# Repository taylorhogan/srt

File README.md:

# Iris — a robotic telescope you talk to

*IC 1396A, the Elephant's Trunk — 12.1 hours across four nights: 145
five-minute exposures through three narrowband filters. Nobody was in the
observatory for any of them.*

Text Iris the name of a nebula from your phone. Some clear night — maybe tonight,
maybe next week when the geometry is right — a roof in a backyard opens on its
own, a half-ton telescope wakes up, finds the target, and spends the dark hours
collecting photons that left their source before the pyramids were built. By
breakfast there is a finished picture on your phone, captioned with how many
frames survived the night's quality gate. Nobody was in the observatory. Nobody
was awake.

That is the whole idea: **a fully autonomous deep-sky observatory run by
conversation**, built on one stubborn principle — *measure it, or it isn't
true*. Every subsystem below exists because a measurement demanded it, and most
of them have caught at least one thing that "looked fine."

The pictures and the write-ups live at **[irisscience.org](https://irisscience.org)**:
a gallery, a lab notebook of about thirty science notes (linked throughout this
page), and a live tab showing what the observatory is doing *right now*, down to
which state of its night state machine it is standing in.

---

## Hubble's experiment, a century later

In October 1923 Edwin Hubble found a Cepheid variable on a plate of the
Andromeda nebula, timed its 31.4-day pulse, and from Henrietta Leavitt's
period–luminosity law measured the distance to another galaxy for the first
time. In the autumn of 2026 Iris ran the same measurement on the same star.

- The star went into the queue on October 8 as a one-hour *monitor* target with
  its period attached. From then on the planner gave it an hour near the zenith
  on every clear night, the frames were calibrated and measured against Gaia
  comparison stars each morning, and the pipeline's own coverage rule decided
  when the curve was complete.
- Twenty-two nights caught the whole cycle: a 1.1-magnitude swing, the first
  maximum, the long decline, and a second climb of a full magnitude in two
  nights. The fitted curve's predictions for coming nights were kept and tested;
  three of four landed within a few hundredths, and the one miss is the most
  instructive line in the note.
- Leavitt's law, as calibrated by Hubble Space Telescope parallaxes, turns the
  period and the mean brightness into **669 kpc, 2.18 million light years**,
  against 2.54 accepted — within a fifth with one star, one filter and a
  17-inch telescope. Hubble, with the 100-inch, got a factor of three too close;
  the difference is a century of calibration, not the glass.
- The nightly measurements are AAVSO-grade (calibrated, saturation-guarded,
  airmass on every record, obstructed frames dropped) and written in the
  association's format for upload.

→ [Hubble's Star, a Century Later](https://irisscience.org/#hubble-v1-distance)
· [First light curves: Hubble's star and three Cepheids in Cassiopeia](https://irisscience.org/#cepheids-first-curves)
· [Three targets a night](https://irisscience.org/#three-slots) (how the hour was found)

---

## Neural networks trained on this sky

There is no clean reference image of the sky, so every network below
manufactures its own training signal from this telescope's own stacks, runs on
the observatory's GPU box, and is held to the same rule as everything else:
**nothing is ever measured from a network's output.** Every number quoted
anywhere comes from the calibrated linear stacks.

| Network | What it learns | Note |
|---|---|---|
| **Noise2Noise denoiser** | A U-Net trained on pairs of noisy stacks of the same field, no clean target ever seen. Runs every morning on the night's stacks; display only. | [Learning to denoise without ever seeing a clean image](https://irisscience.org/#noise2noise) · [The first denoise worth showing](https://irisscience.org/#n2n-first-result) |
| **Learned deconvolution** | Each stack is blurred a second time with its own measured kernel and the network learns to take that blur back off. It does not paint pixels: for every pixel it decides where the light came from and sends it back, so light is moved, never made, and stars go from 7.5 to about 4 px with no rings. Now the default sharpening on every morning render. | [Learning to undo the blur: a network that moves light](https://irisscience.org/#learned-deblur) · [Deconvolving Stephan's Quintet](https://irisscience.org/#quintet-deblur) (the hand-rule version it replaced) |
| **Star / nebula split** | A U-Net that takes a narrowband plane and returns it without its stars; the stars are the difference. Trained on real backgrounds with known stars injected from the field's own star profile. On a field it had never seen it lifted 338 of 358 stars cleanly. | [IC 410 without its stars](https://irisscience.org/#starless-ic410) |
| **Two language models** | An open-weight vision-language model on the observatory's own computer reads the picture and the measured record and drafts the gallery entry in the house voice; a second model from a different lab checks it for errors. Nothing leaves the building. | [Who writes the caption](https://irisscience.org/#machine-caption) |

---

## Other things Iris has actually done

- **Measured a redshift with no spectrograph.** The four distant members of
  Stephan's Quintet recede fast enough that their hydrogen glow lands inside a
  3 nm filter built for sulfur; the foreground galaxy's does not. 56 times the
  noise in NGC 7319, nothing in NGC 7320.
  → [Five galaxies that only look like neighbors](https://irisscience.org/#quintet-redshift)
- **Identified an asteroid that wandered through a frame.** A rainbow of
  dashes under NGC 1055 tracked at 32.6 arcseconds an hour; solved against
  Gaia, it sat 1.3 arcseconds from where JPL put 464 Megaira.
  → [A visitor in the frame](https://irisscience.org/#asteroid-megaira)
- **Detected an exoplanet.** A 7-hour run on HAT-P-32 caught the transit of
  HAT-P-32b; the blind search ranked it first of 622 stars.
  → [Finding a planet by watching a star get 2% fainter](https://irisscience.org/#transit-search)
  · [A search that finds nothing looks exactly like a search that works](https://irisscience.org/#injection)
- **Decides for itself when a target is done and which filters to shoot.**
  A target is retired when its stack has stopped improving *and* every filter
  holds its minimum of good frames; each night's filter ratio goes to whatever
  the stack is shortest of, weighted by noise, seeing and moon. Live since
  November 2026; the first noon retired two targets.
  → [Two decisions the telescope now makes by itself](https://irisscience.org/#auto-stop-filters)
- **Fills the whole night.** Trees bound the sky at 60° west and 48° northeast;
  the planner fits three targets around them, and a light-curve target can ask
  for a single hour.
  → [Three targets a night](https://irisscience.org/#three-slots)
- **Knows where focus will be before it looks.** 580 autofocus runs showed every
  filter's focus follows temperature along a line, about 80 steps per degree;
  each filter block now starts at the model's prediction.
  → [Telling the telescope where focus will be](https://irisscience.org/#focus-seed)
- **Fixed its own color from the stars.** The camera records a fifth more green
  than red or blue for a white star; a few hundred field stars now set the
  white balance of every broadband render.
  → [Why the galaxy came out green, and how the stars fixed it](https://irisscience.org/#star-white-balance)
- **Caught a space station with a $25 camera.** The driveway camera knew the
  pass from that morning's orbital data, armed itself and recorded Tiangong
  through cloud on a night the roof never opened. The same camera is
  plate-solved to 1.5 px and called a real storm 25–40 minutes before the
  weather API.
  → [The $25 camera that caught a space station](https://irisscience.org/#satellite-tracker)
  · [A security camera as a scientific instrument](https://irisscience.org/#skycam)
- **Caught its own tooling lying.** The FITS headers showed the guider's dither
  silently dead in one axis for months; the mount was exonerated by direct
  measurement and the dither now runs through the mount's native API.
  → [Missing on purpose](https://irisscience.org/#dither)
- **Hears and watches its roof.** Every roof move is fingerprinted by sound and
  by a watt-by-watt power trace; a live stall watchdog cut motor power on a
  real gear-didn't-engage event.
  → [Teaching the observatory to hear its own roof failing](https://irisscience.org/#roof-sentry)
  · [The camera that has to be right about the roof](https://irisscience.org/#vision-safety)
- **Weighed a cluster's age, measured its own optics, and worked out what its
  seeing actually depends on** (850 hPa wind and humidity, not the jet stream).
  → [M13's color–magnitude diagram](https://irisscience.org/#hr-diagram)
  · [What shape is a star?](https://irisscience.org/#psf)
  · [Has anything changed, or was it just a bad night?](https://irisscience.org/#optics)
- **Put a status light on the nightstand** so the owner stops unlocking a phone
  at 2 a.m.: a five-centimeter screen that can do nothing but show the frame
  counts and the sky.
  → [A telescope status light for the nightstand](https://irisscience.org/#nightstand-display)

And one essay with no telescope time in it:
[What a year of a great telescope costs, and who pays it](https://irisscience.org/#telescope-cost).

---

## How a night works

1. **Noon** — the conductor's clock makes the decision: every queued target is
   scored by visibility above the measured tree line, air mass, priority and
   the moon, the night is cut into up to three slots, each slot's filter ratio
   is chosen from the frames already on disk and the seeing forecast, and the
   plan is journaled and posted. Disk space on either machine is a stopping item.
2. **Pre-sunset** — weather, safety flags and a fresh camera read are checked
   again; the N.I.N.A sequence is generated from the plan and compared, field
   by field, with what was announced. A mismatch refuses the file rather than
   the night.
3. **Roof open** — only after two cameras agree the scope is parked. The two
   hardware laws are absolute and enforced in code: *the roof never moves unless
   the scope is confirmed parked; the scope never moves unless the roof is
   confirmed open.* Since September 2026 the roof's position is read from an
   AprilTag on the moving truss by a second camera that needs no light, and
   the inside camera may only veto.
4. **The run** — cool, slew, plate-solve, seed the focus from the temperature
   model, autofocus, then light frames until astronomical dawn with a dither
   between subs. Every incoming frame is measured (FWHM, star count, sky) and
   streamed to the chat and the public live page.
5. **Dawn** — flats, park, roof close, dehumidifier on, summary posted. The
   GPU box pulls the night's frames, stacks, denoises, deconvolves, white
   balances and crops, and pushes the picture to a phone. A converged target
   gets a final render with its own quality check, a drafted caption, and a
   chat card that publishes to the gallery on the word `approve`.

The whole night is driven by a formally specified state machine — a data
table with every state × event pair tested, including a 1,944-case sweep that
proves the roof invariant over the entire sensor-evidence space. It shadowed
real nights read-only through the summer; since October 2026 it decides both
hardware invariants and plans the nights, and the legacy scheduler only carries
out what it says. A hold rings the phone until acknowledged, and a held
observatory reminds its owner once a day until released. Deploys are gated the
same way: the observatory pulls a `release` branch that only advances when CI
is green, so a broken push can never reach the roof controls.

---

## Talking to it

The chat runs on a self-hosted web server (excellent from a phone) with live
job cards, frame previews and cancellable long commands. A taste:

| Command | What happens |
|---|---|
| `image <dso>` | Queue a target; it is scheduled when its night comes, typed as galaxy or nebula on the way in |
| `tonight` | Tonight's plan: slots, hours, filters, weather, moon, visible ISS passes |
| `suggest` | Ranked showpieces worth adding, scored on the next 30 nights' visibility, field fit and moon; nothing is queued without an `image` |
| `stats` / `latest` | Per-frame quality plots; the most recent sub, annotated |
| `snr <dso>` | Stack-convergence curves per filter — is this target *done*? |
| `filters <dso> … for N` | An explicit filter plan that expires after N imaged nights |
| `reopen` / `hold` / `moon` / `maxhours` / `type` | The queue's fields as commands; no hand edits of the JSON |
| `process <dso> <recipe>` | Calibrated LRGB / HALRGB / HOO / SHO stack on demand, with palette gain and tone |
| `aavso <dso>` | The monitor's light curve in AAVSO Extended Format |
| `optics` | Per-star fits → FWHM heatmap, coma, tilt and collimation scores from one frame |
| `transit <star>` | Photometric time series and box-fit transit search |
| `overhead` | Aircraft over the roof right now, from the public ADS-B feed |
| `approve <dso>` / `reject <dso>` | The one word that publishes a drafted gallery entry |
| `safe!` / `stop!` / `resolve!` | The human veto, always |

---

## The parts

| Subsystem | What it does |
|---|---|
| `iris/conductor` | The machine-as-data state machine: journal, guards, the clock that plans the night, the bell that rings the phone |
| Scheduler | Carries out the conductor's plan: generation, verification, imaging, shutdown |
| Vision safety | AprilTags on the scope and the roof, read by two cameras; the north camera decides the roof, the inside camera may veto |
| Frame watcher | Live FWHM / star count / sky analysis of every sub as it lands |
| Sequence generator | Patches N.I.N.A templates with target, coordinates, per-filter gain, focus seed and the planned filter ratio, then verifies the file against the announcement |
| Stacker | Calibration matched to the lights' gain, quality gate, astroalign registration in a process pool, tiled sigma-clip that levels frames to a common sky (skipping that step measured **8× worse than the photon limit**) |
| Color pipeline | Shared reference and shared stretch across filters, Hα excess into LRGB, palette gain, star-neutral palettes, star white balance, color planes matched to one star width, four-stage background removal |
| Photometry | Nightly light curves against Gaia comparison stars, phase coverage, Leavitt-law distance, AAVSO export |
| Auto-stop, filter advisor, suggestions | The three decisions that used to need a person every few days |
| Audio + current sentry | Spectrogram matching and power-signature analysis of every roof move, plus the live stall watchdog |
| Sky cameras | An all-sky fisheye and a plate-solved consumer cam: cloud cover, rain detection, satellite passes, limiting magnitude |
| Publisher | The live page, the target board, final renders with QC, drafted captions, the approve gate, the gallery |
| `nn/` | Noise2Noise, learned deconvolution and the star split: training and nightly inference on a DGX Spark |

Hardware: PlaneWave CDK17 on an L-500 direct-drive mount, a 61 MP full-frame
mono camera with a 7-filter wheel, a sliding roof driven by a gate-opener motor,
TP-Link/Shelly switched power, cameras and a microphone as senses, an NVIDIA
DGX Spark for the networks — all behind Tailscale, with the public face served
through a Cloudflare tunnel.

---

## A word of honesty before you clone

This is open source, but it is not (yet) a product. Iris is one specific
observatory — one roof, one mount, one camera, one tree line, and a hundred
constants measured against them. Paths, wheel positions, park coordinates,
horizon profiles and marker positions all assume *this* backyard. You could
absolutely build your own from these pieces, and the code tries hard to keep
its reasoning legible for exactly that reader — but expect to bring a measuring
instinct rather than run an installer. The conductor is the part that has
already crossed over: a machine defined as data, separated from the
measurements that feed it, which another observatory could actually adopt.

---

## Setup

```bash
# Install uv (once)
curl -LsSf https://astral.sh/uv/install.sh | sh

# Clone the repo
git clone https://github.com/taylorhogan/srt.git
cd srt

# Create and activate virtualenv (Python 3.13+).
# Use uv's default .venv path — `uv pip` auto-discovers it; a differently
# named venv is silently ignored and parts of the pipeline degrade quietly.
uv venv --python 3.13
source .venv/bin/activate      # Linux / macOS
# .venv\Scripts\activate       # Windows (what the observatory itself runs)

# Install dependencies
uv pip install -r requirements.txt

# Create private config (required before running anything)
cp configs/config_blank_private.py configs/config_private.py
# Then fill in API keys/tokens in config_private.py
```

## Running

```bash
# Start both the chat server and the scheduler together
python end_points/start_srt.py

# Or run individually:
python end_points/scheduler_server.py   # Nightly state machine
python cmd_processing/social_server.py  # Web chat server
```

Operations, alerts and what to do about each are in `docs/HANDBOOK.md`; what
dies when each account lapses, and how to restore, in `docs/SUCCESSION.md`.

---

## Appreciation

This work rests heavily on others:
- [Astropy](https://www.astropy.org) / [Astroplan](https://astroplan.readthedocs.io) / [astroquery](https://astroquery.readthedocs.io) — and the [SIMBAD](https://simbad.cds.unistra.fr) service at CDS behind it
- [Gaia](https://www.cosmos.esa.int/gaia) (ESA) — every comparison star and every astrometric solution
- [N.I.N.A](https://nighttime-imaging.eu)
- [astroalign](https://astroalign.quatrope.org) / [SEP](https://sep.readthedocs.io) / [photutils](https://photutils.readthedocs.io)
- [python-kasa](https://github.com/python-kasa/python-kasa) — vendored in this very repo to switch the observatory's power
- [Open-Meteo](https://open-meteo.com) and the US National Weather Service — forecasts, no key required, asked every single day
- [Skyfield](https://rhodesmill.org/skyfield/) — satellite passes and ephemerides
- [OpenCV](https://opencv.org) and [AprilTag](https://april.eecs.umich.edu/software/apriltag) — the vision safety system's eyes
- [librosa](https://librosa.org) — the roof sentry's ears (mel spectrograms)
- [PyTorch](https://pytorch.org) — every network above
- [Ollama](https://ollama.com), Gemma and Qwen — the caption writer and its critic, on the observatory's own computer
- [FastAPI](https://fastapi.tiangolo.com) / [uvicorn](https://www.uvicorn.org) — the chat server
- [Noise2Noise](https://arxiv.org/abs/1803.04189) (Lehtinen et al., 2018)
- [AAVSO](https://www.aavso.org) — the variable-star charts, the comparison sequences and the place the light curves go
- [Allsky](https://github.com/thomasjacquin/allsky)
- [Claude](https://claude.com/claude-code) (Anthropic) — pair programmer for much of what's described above, from the stacking mathematics to the state machines to this README

---

*Iris Observatory · Social Robotic Telescope · nobody is awake, and the roof
just opened anyway*

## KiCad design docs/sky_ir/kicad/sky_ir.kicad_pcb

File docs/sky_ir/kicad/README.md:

# Sky IR sensor carrier board (KiCad)

A KiCad project for the sky IR sensor: the ESP32-S3-DevKitC-1 plugs into two 1x22 sockets on a small carrier that holds the I2C pull-ups, the heater MOSFET and its gate parts, and pin headers for the three things that live off the board on leads: the MLX90614 (it must see the sky), the BME280 breakout and the 47 ohm window heater. Electrically it is the same circuit as `../sky_ir_wiring_print.html`; the firmware is `../sky-ir.yaml`.

Checked with KiCad 10.0.8 on 2026-11-17: ERC 0 violations, DRC 0 violations, 0 unconnected items, 0 schematic parity issues, zones filled. Gerbers and the drill file are in `gerbers/`.

## Files

| File | What |
|---|---|
| `sky_ir.kicad_pro` | project (open this) |
| `sky_ir.kicad_sch` | schematic, one sheet, nets by global label |
| `sky_ir.kicad_pcb` | board, 70.9 x 72 mm, two layers, routed, GND pour on the back |
| `sky_ir.kicad_sym`, `sky_ir.pretty/` | the project's own symbols and footprints, wired in by `sym-lib-table` / `fp-lib-table` |
| `gerbers/` | F/B copper, mask, silk, edge cuts, Excellon drill, job file |
| `board.png`, `board_bottom.png`, `sch.png` | KiCad's renders |
| `gen_a.py`, `gen_b.py` | the generator that wrote the files (`python3 gen_a.py out && python3 gen_b.py out`) |

## Circuit

| Ref | Part | Nets |
|---|---|---|
| U1 | ESP32-S3-DevKitC-1 (N16R8) in two 1x22 female headers | 3V3 (pins 1-2), GPIO8 SDA, GPIO9 SCL, GPIO10 gate, 5V, GND |
| R1, R2 | 4.7 k | SDA and SCL pull-ups to 3V3 |
| R3 | 220 R | GPIO10 to the MOSFET gate |
| R4 | 10 k | gate to GND (holds the heater off at boot) |
| Q1 | IRLZ44N, TO-220, G D S | low-side switch for the heater |
| J2 | 1x04 header | MLX90614 leads: VDD GND SCL SDA |
| J4 | 1x04 header | BME280 breakout: VIN GND SCL SDA |
| J5 | 1x02 header | heater: +5V, drain |
| H1-H4 | 3.2 mm holes | M3 standoffs |

Unused DevKit pins are left open on purpose (no-connect flags in the schematic).

## Before ordering

1. **Socket row spacing.** The two DevKit columns are drawn 22.86 mm (0.9 in) apart. Measure pin 1 of each row on your board; if it differs, change `ROW` at the top of `gen_a.py`, rerun both generators and re-export, or move J3's column in the board editor. Everything this build uses is in the left column, so the right socket is mechanical only.
2. The DevKit's USB-C connectors overhang the socket end marked on the silkscreen; leave that board edge clear in the box.
3. The IRLZ44N tab is the drain: do not bolt it to a grounded box wall without an insulator.

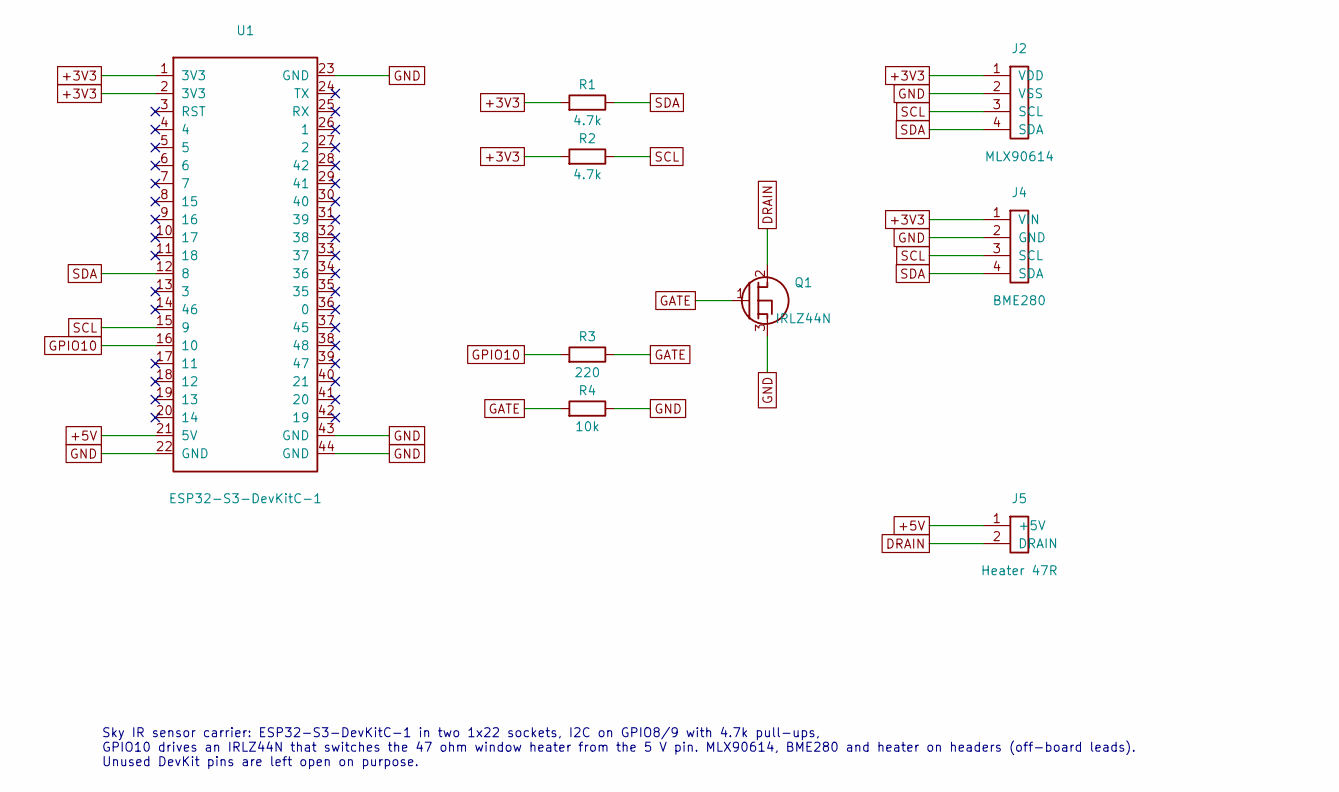
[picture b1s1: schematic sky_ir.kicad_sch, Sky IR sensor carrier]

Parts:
J2: MLX90614; PinHeader_1x04
J4: BME280; PinHeader_1x04
J5: Heater 47R; PinHeader_1x02
Q1: IRLZ44N; TO-220-3_Vertical
R1, R2: 4.7k; R_Axial_P10.16mm
R3: 220; R_Axial_P10.16mm
R4: 10k; R_Axial_P10.16mm
U1: ESP32-S3-DevKitC-1; ESP32-S3-DevKitC-1_Sockets

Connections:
+3V3: J2.1 (VDD), J4.1 (VIN), R1.1, R2.1, U1.1 (3V3), U1.2 (3V3)
+5V: J5.1 (+5V), U1.21 (5V)
DRAIN: J5.2 (DRAIN), Q1.2 (D)
GATE: Q1.1 (G), R3.2, R4.1
GND: J2.2 (VSS), J4.2 (GND), Q1.3 (S), R4.2, U1.22 (GND), U1.23 (GND), U1.43 (GND), U1.44 (GND)
GPIO10: R3.1, U1.16 (10)
SCL: J2.3 (SCL), J4.3 (SCL), R2.2, U1.15 (9)
SDA: J2.4 (SDA), J4.4 (SDA), R1.2, U1.12 (8)

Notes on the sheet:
Sky IR sensor carrier: ESP32-S3-DevKitC-1 in two 1x22 sockets, I2C on GPIO8/9 with 4.7k pull-ups, GPIO10 drives an IRLZ44N that switches the 47 ohm window heater from the 5 V pin. MLX90614, BME280 and heater on headers (off-board leads). Unused DevKit pins are left open on purpose.

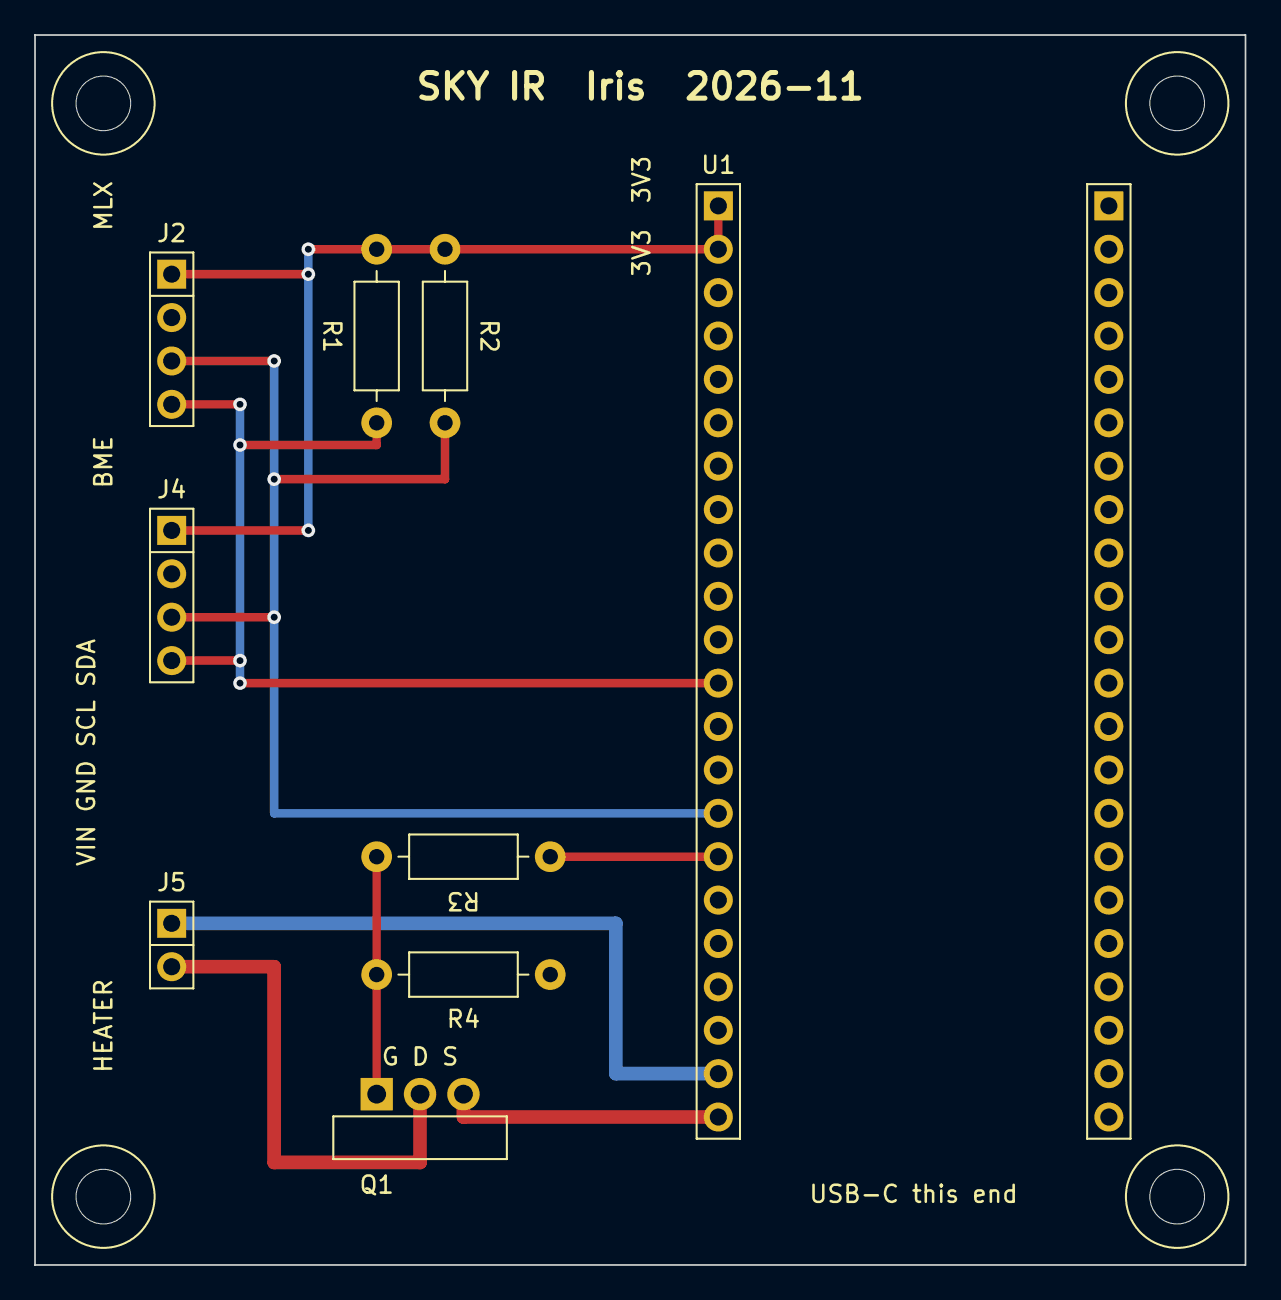
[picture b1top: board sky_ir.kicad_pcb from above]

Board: 2 copper layers, 70.9 x 72.0 mm, 13 parts (0 on the bottom side), 8 nets.

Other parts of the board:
H1, H2, H3, H4: M3; MountingHole_3.2mm
